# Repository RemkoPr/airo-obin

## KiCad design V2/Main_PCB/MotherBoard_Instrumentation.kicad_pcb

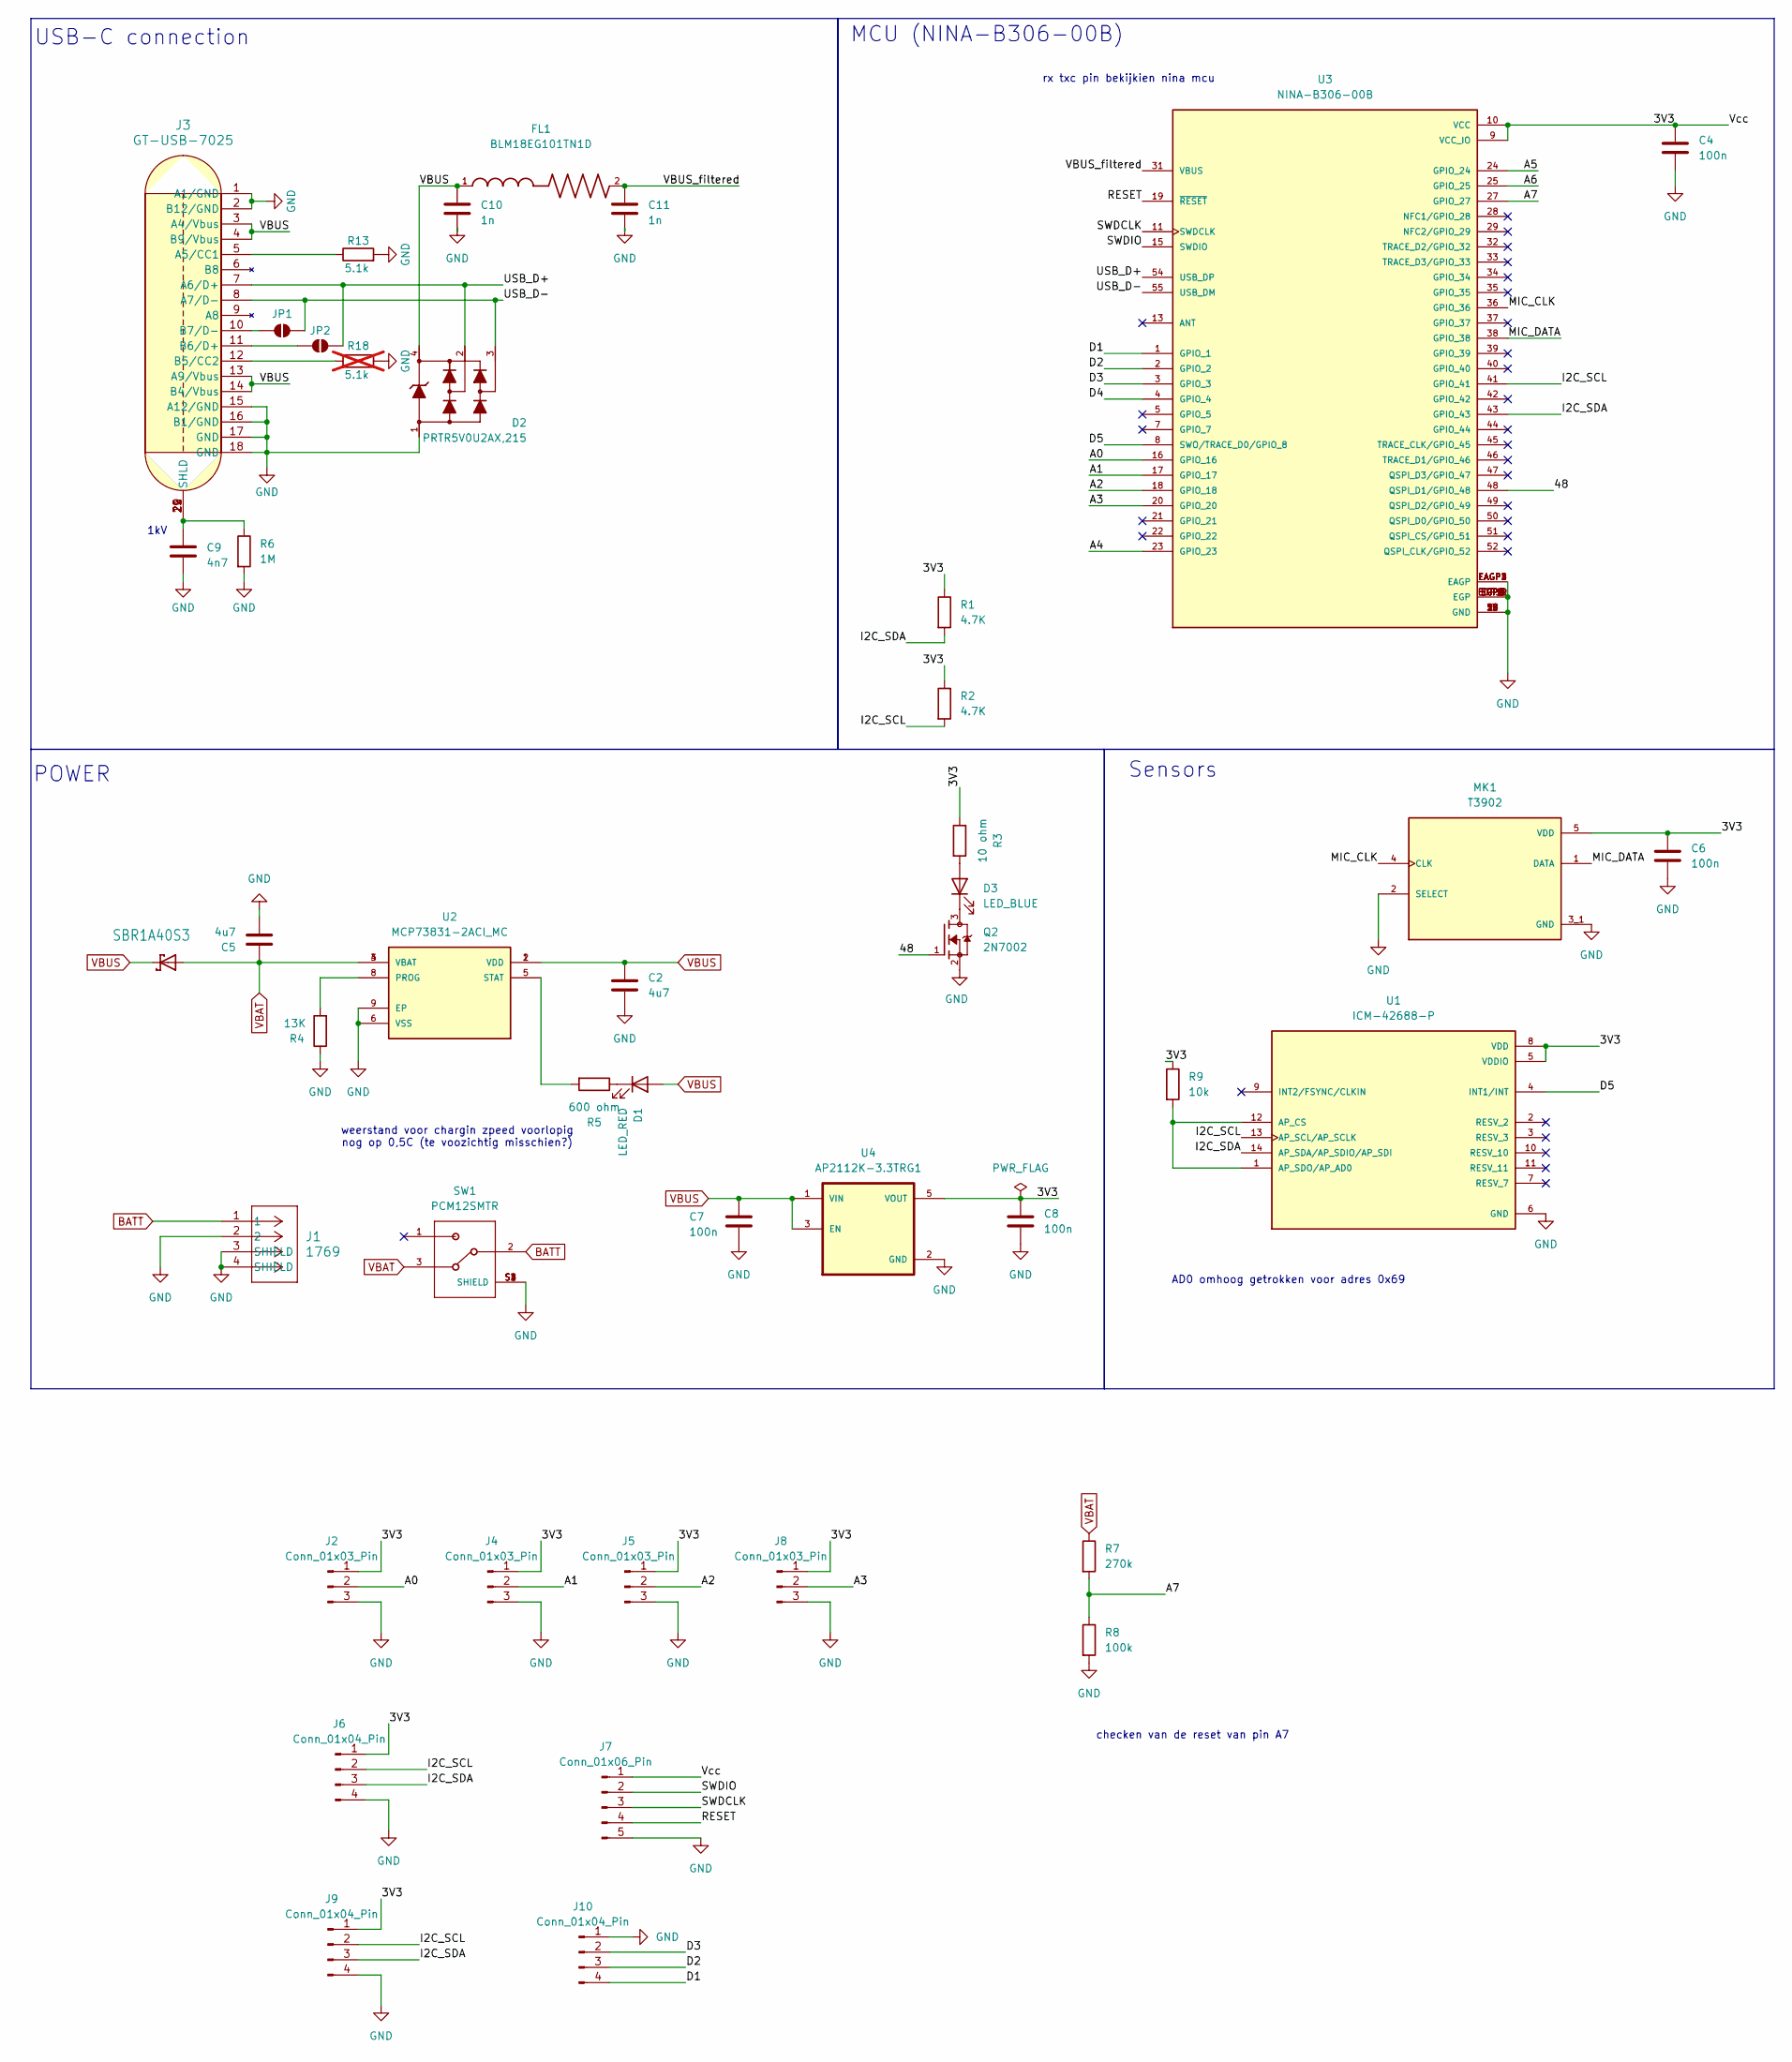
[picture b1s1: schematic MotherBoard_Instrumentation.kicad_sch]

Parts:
C2, C5: 4u7; C_0402_1005Metric; LCSC C23687
C4, C6, C7, C8: 100n; C_0402_1005Metric; LCSC C1525
C9: 4n7; C_0402_1005Metric; LCSC C1538
C10, C11: 1n; C_0402_1005Metric; LCSC C1523
D1: LED_RED; LED_0805_2012Metric; LCSC C5156920
D2: PRTR5V0U2AX,215; ESD_PROT_SOT143B; LCSC C455074
D3: LED_BLUE; LED_0805_2012Metric; LCSC C6067133
FL1: BLM18EG101TN1D; C_0603_1608Metric; LCSC C76893
J1: 1769; CONN_S2B-PH-SM4-TB_JST; LCSC C295747
J2, J4, J5, J8: Conn_01x03_Pin; 3_holes_castellated
J3: GT-USB-7025; CONN16X1_GT-USB-7025_GSW
J6, J9: Conn_01x04_Pin; castellated_hole_4
J7: Conn_01x06_Pin; 5_pads_2.54_pitch
J10: Conn_01x04_Pin; PinHeader_1x04_P2.54mm_Vertical
JP1, JP2: SolderJumper_2_Open; SolderJumper-2_P1.3mm_Open_RoundedPad1.0x1.5mm
MK1: T3902; MIC_T3902; PARTREV 1.0; LCSC C3171752
Q2: 2N7002; SOT95P240X111-3N; PARTREV 4; LCSC C8545
R1, R2: 4.7K; R_0402_1005Metric; LCSC C25900
R3: 10 ohm; R_0402_1005Metric; LCSC C25077
R4: 13K; R_0402_1005Metric; LCSC C11788
R5: 600 ohm; R_0402_1005Metric; LCSC C25130
R6: 1M; R_0402_1005Metric; LCSC C26083
R7: 270k; R_0402_1005Metric; LCSC C25550
R8: 100k; R_0402_1005Metric; LCSC C25530
R9: 10k; R_0402_1005Metric; LCSC C25531
R13: 5.1k; R_0402_1005Metric; LCSC C25905
R18: 5.1k; R_0402_1005Metric; not fitted
SBR1A40S1: SBR1A40S3; Shotky_SOD2513X120N; LCSC C460745
SW1: PCM12SMTR; SW_PCM12SMTR; LCSC C221841
U1: ICM-42688-P; ICM_42668; PARTREV 1.2; LCSC C1850418
U2: MCP73831-2ACI_MC; MCP73831; PARTREV G; LCSC C150772
U3: NINA-B306-00B; XCVR_NINA-B306-00B; PARTREV R07; LCSC C6127317
U4: AP2112K-3.3TRG1; AP2112K-3.3; PARTREV 2-2; LCSC C51118

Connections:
/3V3: C4.1, C6.1, C8.1, J2.1, J4.1, J5.1, J6.1, J7.1, J8.1, J9.1, MK1.5 (VDD), R1.1, R2.1, R3.1, R9.1, U1.5 (VDDIO), U1.8 (VDD), U3.9 (VCC_IO), U3.10 (VCC), U4.5 (VOUT)
/48: Q2.1, U3.48 (QSPI_D1/GPIO_48)
/A0: J2.2, U3.16 (GPIO_16)
/A1: J4.2, U3.17 (GPIO_17)
/A2: J5.2, U3.18 (GPIO_18)
/A3: J8.2, U3.20 (GPIO_20)
/A4: U3.23 (GPIO_23)
/A5: U3.24 (GPIO_24)
/A6: U3.25 (GPIO_25)
/A7: R7.2, R8.1, U3.27 (GPIO_27)
/D1: J10.4, U3.1 (GPIO_1)
/D2: J10.3, U3.2 (GPIO_2)
/D3: J10.2, U3.3 (GPIO_3)
/D4: U3.4 (GPIO_4)
/D5: U1.4 (INT1/INT), U3.8 (SWO/TRACE_D0/GPIO_8)
/I2C_SCL: J6.2, J9.2, R2.2, U1.13 (AP_SCL/AP_SCLK), U3.41 (GPIO_41)
/I2C_SDA: J6.3, J9.3, R1.2, U1.14 (AP_SDA/AP_SDIO/AP_SDI), U3.43 (GPIO_43)
/MIC_CLK: MK1.4 (CLK), U3.36 (GPIO_36)
/MIC_DATA: MK1.1 (DATA), U3.38 (GPIO_38)
/RESET: J7.4, U3.19 (~RESET)
/SWDCLK: J7.3, U3.11 (SWDCLK)
/SWDIO: J7.2, U3.15 (SWDIO)
/USB_D+: D2.2, J3.7 (A6/D+), JP2.2 (B), U3.54 (USB_DP)
/USB_D-: D2.3, J3.8 (A7/D-), JP1.2 (B), U3.55 (USB_DM)
/VBUS_filtered: C11.1, FL1.2, U3.31 (VBUS)
BATT: J1.1, SW1.2
GND: C2.2, C4.2, C5.2, C6.2, C7.2, C8.2, C9.2, C10.2, C11.2, D2.1, J1.2, J1.3 (SHIELD), J1.4 (SHIELD), J2.3, J3.1 (A1/GND), J3.2 (B12/GND), J3.15 (A12/GND), J3.16 (B1/GND), J3.17 (GND), J3.18 (GND), J4.3, J5.3, J6.4, J7.5, J8.3, J9.4, J10.1, MK1.2 (SELECT), MK1.3_1 (GND), MK1.3_2 (GND), Q2.2, R4.1, R6.2, R8.2, R13.2, R18.2, SW1.S1 (SHIELD), SW1.S2 (SHIELD), SW1.S3 (SHIELD), SW1.S4 (SHIELD), U1.6 (GND), U2.6 (VSS), U2.9 (EP), U3.6 (GND), U3.12 (GND), U3.14 (GND), U3.26 (GND), U3.30 (GND), U3.53 (GND), U3.EAGP1 (EAGP), U3.EAGP2 (EAGP), U3.EAGP3 (EAGP), U3.EAGP4 (EAGP), U3.EGP1 (EGP), U3.EGP2 (EGP), U3.EGP3 (EGP), U3.EGP4 (EGP), U3.EGP5 (EGP), U3.EGP6 (EGP), U3.EGP7 (EGP), U3.EGP8 (EGP), U3.EGP9 (EGP), U3.EGP10 (EGP), U3.EGP11 (EGP), U3.EGP12 (EGP), U4.2 (GND); also elsewhere on the board
unnamed: C9.1, J3.19 (SHLD), J3.20 (SHLD), J3.21 (SHLD), J3.22 (SHLD), R6.1
unnamed: D1.1 (K), R5.1
unnamed: D3.2 (A), R3.2
unnamed: D3.1 (K), Q2.3
unnamed: J3.5 (A5/CC1), R13.1
unnamed: J3.12 (B5/CC2), R18.1
unnamed: J3.11 (B6/D+), JP2.1 (A)
unnamed: J3.10 (B7/D-), JP1.1 (A)
unnamed: R9.2, U1.1 (AP_SDO/AP_AD0), U1.12 (AP_CS)
unnamed: R4.2, U2.8 (PROG)
unnamed: R5.2, U2.5 (STAT)
VBAT: C5.1, R7.1, SBR1A40S1.A, SW1.3, U2.3 (VBAT), U2.4 (VBAT); also elsewhere on the board
VBUS: C2.1, C7.1, C10.1, D1.2 (A), D2.4, FL1.1, J3.3 (A4/Vbus), J3.4 (B9/Vbus), J3.13 (A9/Vbus), J3.14 (B4/Vbus), SBR1A40S1.C, U2.1 (VDD), U2.2 (VDD), U4.1 (VIN), U4.3 (EN); also elsewhere on the board

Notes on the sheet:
rx txc pin bekijkien nina mcu
POWER
MCU (NINA-B306-00B)
AD0 omhoog getrokken voor adres 0x69
Sensors
1kV
weerstand voor chargin zpeed voorlopig nog op 0,5C (te voozichtig misschien?)
USB-C connection
checken van de reset van pin A7

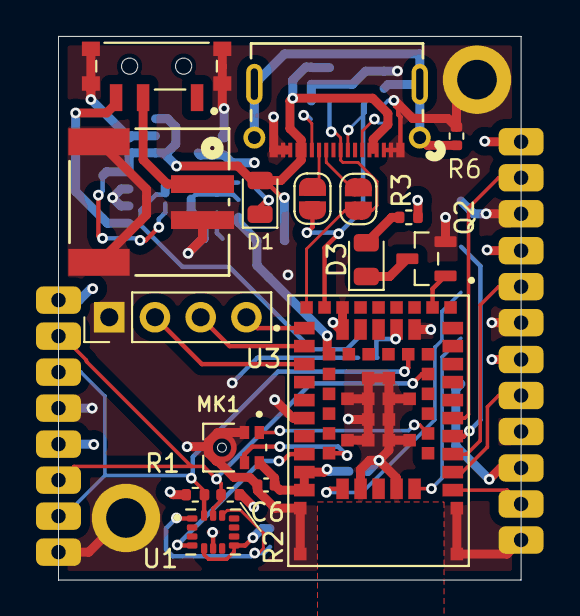
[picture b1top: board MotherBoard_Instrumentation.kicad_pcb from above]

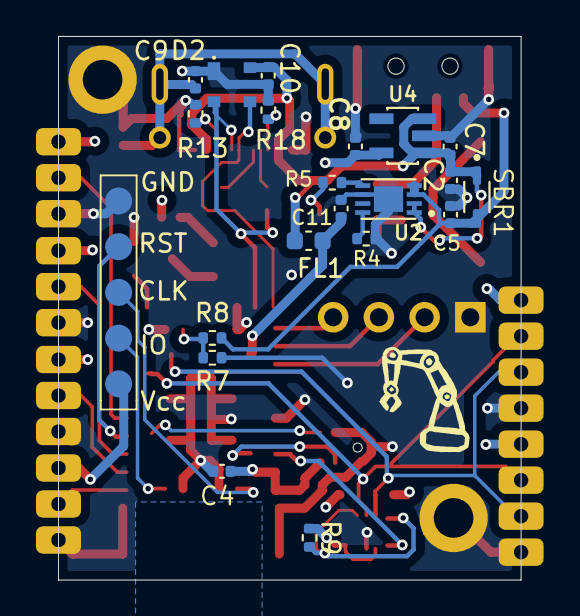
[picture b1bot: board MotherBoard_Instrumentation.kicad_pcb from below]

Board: 4 copper layers, 25.7 x 30.2 mm, 46 parts (21 on the bottom side), 36 nets.

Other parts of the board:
REF: MountingHole_2.2mm_M2_DIN965_Pad
REF#2: MountingHole_2.2mm_M2_DIN965_Pad
SBR1: SBR1A40S3; Shotky_SOD2513X120N

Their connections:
GND: REF.1, REF#2.1; also elsewhere on the board
VBAT: SBR1.A; also elsewhere on the board
VBUS: SBR1.C; also elsewhere on the board

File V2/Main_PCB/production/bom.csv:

Designator,Footprint,Quantity,Value,LCSC Part #
"C10, C11",0402,2,1n,C1523
"C2, C5",0402,2,4u7, C23687
"C4, C6, C7, C8",0402,4,100n,C1525
C9,0402,1,4n7,C1538
D1,0805,1,LED_RED,C5156920
D2,ESD_PROT_SOT143B,1,"PRTR5V0U2AX,215",C455074
D3,0805,1,LED_BLUE,C6067133
FL1,0603,1,BLM18EG101TN1D,C76893
J1,CONN_S2B-PH-SM4-TB_JST,1,1769,C295747
J10,PinHeader_1x04_P2.54mm_Vertical,1,Conn_01x04_Pin,
"J2, J4, J5, J8",3_holes_castellated,4,Conn_01x03_Pin,
J3,CONN16X1_GT-USB-7025_GSW,1,GT-USB-7025,C963213
"J6, J9",castellated_hole_4,2,Conn_01x04_Pin,
J7,5_pads_2.54_pitch,1,Conn_01x06_Pin,
MK1,MIC_T3902,1,T3902, C3171752
Q2,SOT95P240X111-3N,1,2N7002, C8545
"R1, R2",0402,2,4.7K,C25900
R13,0402,1,5.1k,C25905
R18,0402,1,5.1k,
R3,0402,1,10 ohm,C25077
R4,0402,1,13K,C11788
R5,0402,1,600 ohm,C25130
R6,0402,1,1M, C26083
R7,0402,1,270k,C25550
R8,0402,1,100k,C25530
R9,0402,1,10k,C25531
SBR1,Shotky_SOD2513X120N,1,SBR1A40S3,C460745
SW1,SW_PCM12SMTR,1,PCM12SMTR,C221841
U1,ICM_42668,1,ICM-42688-P,C1850418
U2,MCP73831,1,MCP73831-2ACI_MC,C150772
U3,XCVR_NINA-B306-00B,1,NINA-B306-00B,C6127317
U4,AP2112K-3.3,1,AP2112K-3.3TRG1,C51118

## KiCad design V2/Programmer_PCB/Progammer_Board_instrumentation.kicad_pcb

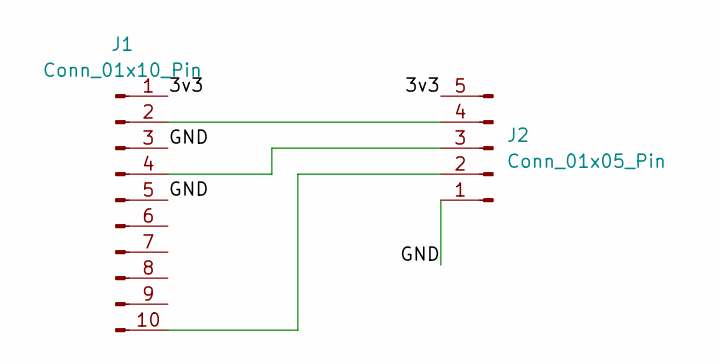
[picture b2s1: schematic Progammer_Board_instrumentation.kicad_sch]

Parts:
J1: Conn_01x10_Pin; PinHeader_2x05_P1.27mm_Vertical
J2: Conn_01x05_Pin; PinHeader_1x05_P2.54mm_Vertical

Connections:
/3v3: J1.1, J2.5
/GND: J1.3, J1.5, J2.1
unnamed: J1.2, J2.4
unnamed: J1.4, J2.3
unnamed: J1.10, J2.2

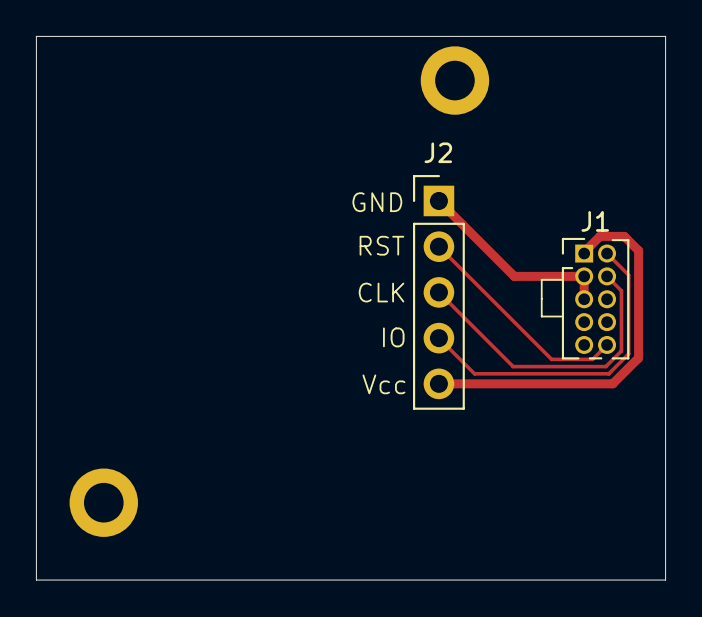
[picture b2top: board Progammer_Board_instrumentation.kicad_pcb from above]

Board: 2 copper layers, 34.9 x 30.2 mm, 4 parts (0 on the bottom side), 5 nets.

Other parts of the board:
REF: MountingHole_2.2mm_M2_DIN965_Pad
REF#2: MountingHole_2.2mm_M2_DIN965_Pad

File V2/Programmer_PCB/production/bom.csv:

Designator,Footprint,Quantity,Value,LCSC Part #
J1,PinHeader_2x05_P1.27mm_Vertical,1,Conn_01x10_Pin,
J2,PinHeader_1x05_P2.54mm_Vertical,1,Conn_01x05_Pin,

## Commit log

2026-04-26 V1-upload
2026-04-29 V2_added
    added the V2 version of the instrumentation PCB.
